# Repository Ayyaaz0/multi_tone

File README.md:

A three-band music visualiser. It takes audio signals, splits them into low (bass), mid (voice), and high (treble) bands using op-amp filters, converts each band’s loudness into a smooth control signal, and drives three LEDs via 2N3904 transistors. The circuit runs from a regulated ±12 V supply.

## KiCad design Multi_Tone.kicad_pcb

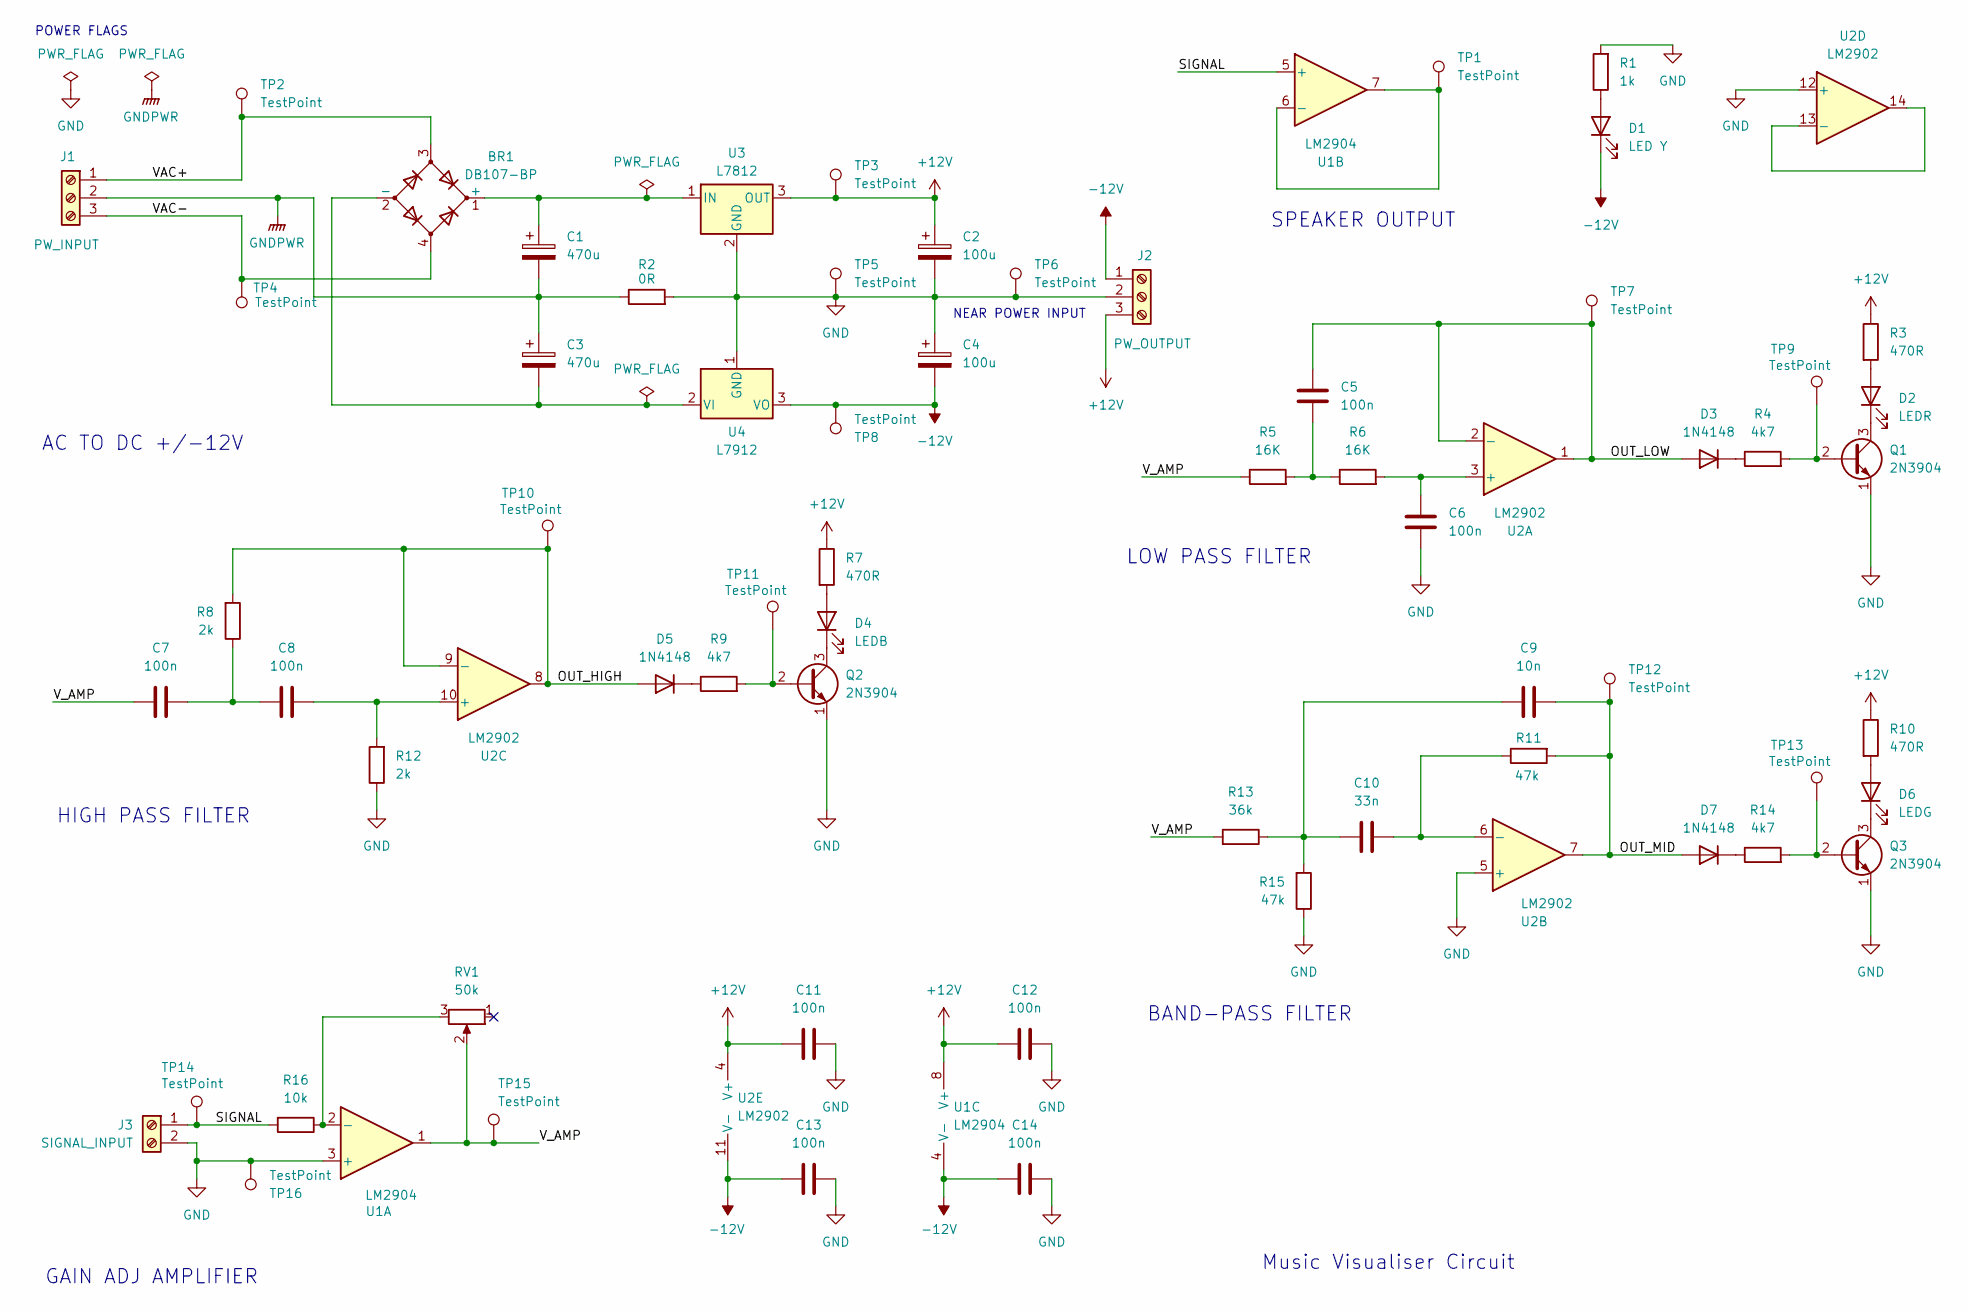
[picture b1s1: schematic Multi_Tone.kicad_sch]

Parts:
BR1: DB107-BP; Diode_Bridge_DIP-4_W7.62mm_P5.08mm
C1, C3: 470u; CP_Radial_D8.0mm_P3.50mm
C2, C4: 100u; CP_Radial_D8.0mm_P3.50mm
C5, C6, C7, C8, C11, C12, C13, C14: 100n; C_Rect_L7.0mm_W2.5mm_P5.00mm
C9: 10n; C_Rect_L7.0mm_W2.5mm_P5.00mm
C10: 33n; C_Rect_L7.0mm_W2.5mm_P5.00mm
D1: LED Y; LED_D3.0mm
D2: LEDR; LED_D3.0mm
D3, D5, D7: 1N4148; D_DO-35_SOD27_P7.62mm_Horizontal
D4: LEDB; LED_D3.0mm
D6: LEDG; LED_D3.0mm
J1: PW_INPUT; TerminalBlock_Phoenix_MKDS-1,5-3-5.08_1x03_P5.08mm_Horizont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
J2: PW_OUTPUT; TerminalBlock_Phoenix_MKDS-1,5-3-5.08_1x03_P5.08mm_Horizont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
J3: SIGNAL_INPUT; TerminalBlock_Phoenix_MKDS-1,5-2-5.08_1x02_P5.08mm_Horizont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
Q1, Q2, Q3: 2N3904; TO-92_Inline
R1: 1k; R_Axial_DIN0207_L6.3mm_D2.5mm_P10.16mm_Horizontal
R2: 0R; R_2512_6332Metric
R3, R7, R10: 470R; R_2512_6332Metric
R4, R9, R14: 4k7; R_2512_6332Metric
R5, R6: 16K; R_Axial_DIN0207_L6.3mm_D2.5mm_P10.16mm_Horizontal
R8, R12: 2k; R_Axial_DIN0207_L6.3mm_D2.5mm_P10.16mm_Horizontal
R11, R15: 47k; R_Axial_DIN0207_L6.3mm_D2.5mm_P10.16mm_Horizontal
R13: 36k; R_Axial_DIN0207_L6.3mm_D2.5mm_P10.16mm_Horizontal
R16: 10k; R_Axial_DIN0207_L6.3mm_D2.5mm_P10.16mm_Horizontal
RV1: 50k; Potentiometer_Bourns_3299W_Vertical
TP1, TP2, TP3, TP4, TP5, TP6, TP7, TP8, TP9, TP10, TP11, TP12, TP13, TP14, TP15, TP16: TestPoint; PinHeader_1x01_P2.54mm_Vertical
U1: LM2904; DIP-8_W7.62mm
U2: LM2902; DIP-14_W7.62mm
U3: L7812; TO-220-3_Vertical
U4: L7912; TO-220-3_Vertical

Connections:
+12V: C2.1, C11.1, C12.1, J2.3, R3.1, R7.1, R10.1, TP3.1, U1.8 (V+), U2.4 (V+), U3.3 (OUT)
-12V: C4.2, C13.2, C14.2, D1.1 (K), J2.1, TP8.1, U1.4 (V-), U2.11 (V-), U4.3 (VO)
/OUT_HIGH: D5.2 (A), R8.2, TP10.1, U2.8, U2.9 (-)
/OUT_LOW: C5.1, D3.2 (A), TP7.1, U2.1, U2.2 (-)
/OUT_MID: C9.2, D7.2 (A), R11.2, TP12.1, U2.7
/SIGNAL: J3.1, R16.2, TP14.1, U1.5 (+)
/V_AMP: C7.1, R5.1, R13.2, RV1.2, TP15.1, U1.1
GND: C2.2, C4.1, C6.2, C11.2, C12.2, C13.1, C14.1, J2.2, J3.2, Q1.1 (E), Q2.1 (E), Q3.1 (E), R1.2, R2.2, R12.1, R15.1, TP5.1, TP6.1, TP16.1, U1.3 (+), U2.5 (+), U2.12 (+), U3.2 (GND), U4.1 (GND)
GNDPWR: C1.2, C3.1, J1.2, R2.1
unnamed: BR1.1 (+), C1.1, U3.1 (IN)
unnamed: BR1.2 (-), C3.2, U4.2 (VI)
unnamed: C5.2, R5.2, R6.1
unnamed: C7.2, C8.1, R8.1
unnamed: C9.1, C10.1, R13.1, R15.2
unnamed: D1.2 (A), R1.1
unnamed: D2.2 (A), R3.2
unnamed: D2.1 (K), Q1.3 (C)
unnamed: D3.1 (K), R4.1
unnamed: D4.2 (A), R7.2
unnamed: D4.1 (K), Q2.3 (C)
unnamed: D5.1 (K), R9.1
unnamed: D6.2 (A), R10.2
unnamed: D6.1 (K), Q3.3 (C)
unnamed: D7.1 (K), R14.1
unnamed: BR1.3, J1.1, TP2.1
unnamed: BR1.4, J1.3, TP4.1
unnamed: Q1.2 (B), R4.2, TP9.1
unnamed: Q2.2 (B), R9.2, TP11.1
unnamed: Q3.2 (B), R14.2, TP13.1
unnamed: R16.1, RV1.3, U1.2 (-)
unnamed: TP1.1, U1.6 (-), U1.7
unnamed: C6.1, R6.2, U2.3 (+)
unnamed: C10.2, R11.1, U2.6 (-)
unnamed: C8.2, R12.2, U2.10 (+)
unnamed: U2.13 (-), U2.14

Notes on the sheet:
NEAR POWER INPUT
BAND-PASS FILTER
Music Visualiser Circuit
GAIN ADJ AMPLIFIER
AC TO DC +/-12V
HIGH PASS FILTER
POWER FLAGS
SPEAKER OUTPUT
LOW PASS FILTER

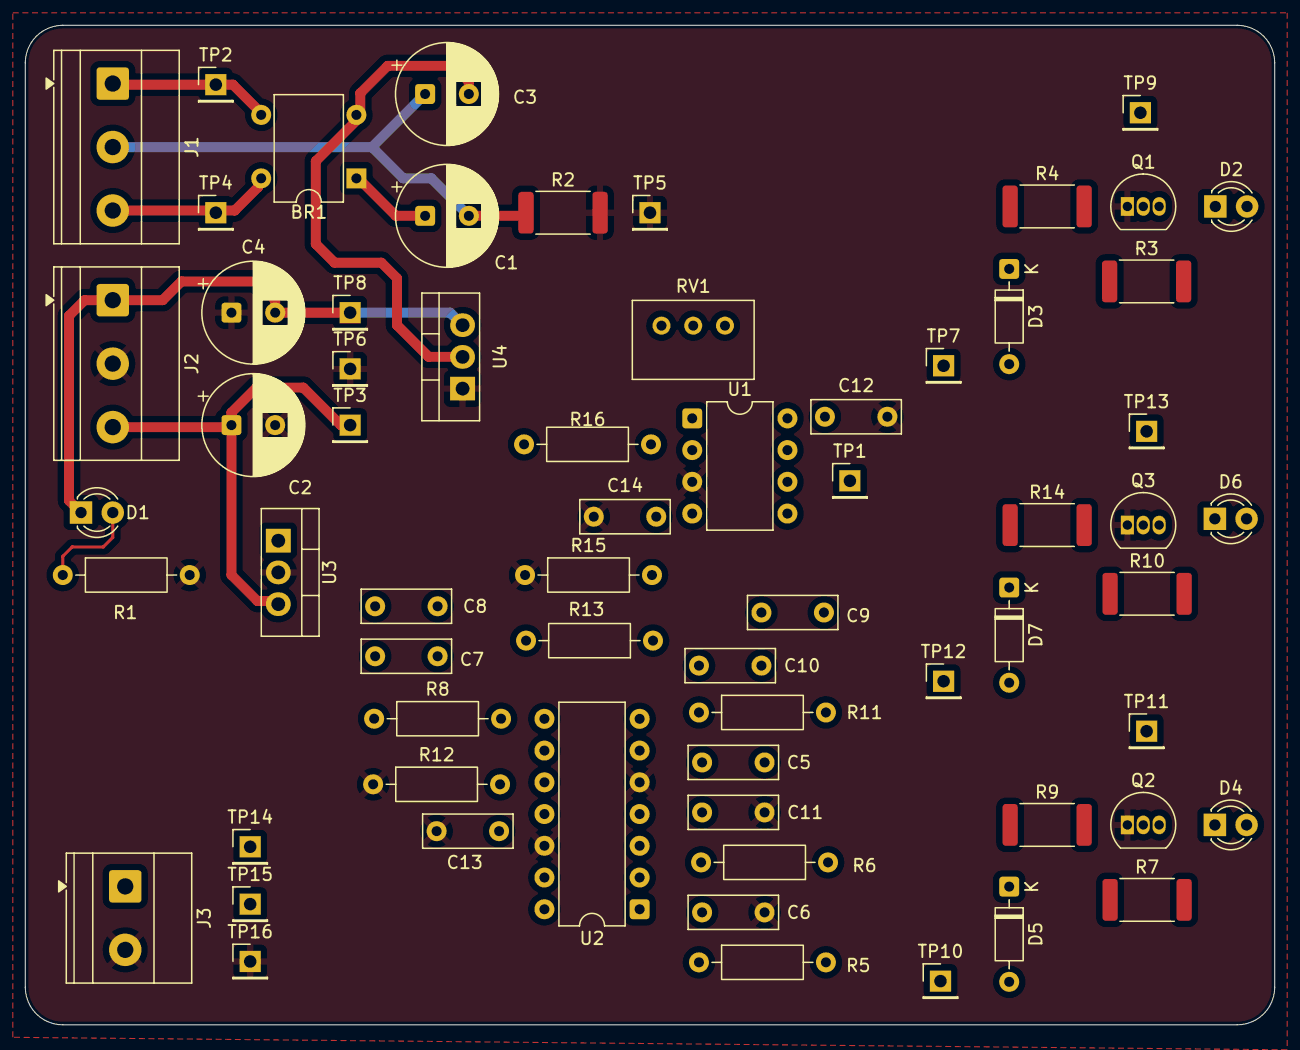
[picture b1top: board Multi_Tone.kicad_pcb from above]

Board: 2 copper layers, 100.0 x 80.0 mm, 65 parts (0 on the bottom side), 35 nets.

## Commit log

2026-02-06 Initial KiCad project
2026-02-08 Added band-pass filter, ac-dc power, low-pass filter
2026-02-13 Completed schematic layout of music visualiser circuit.
2026-02-13 Added footprints to schematic and changed band-pass filter resistor to 47k (R11)
2026-02-18 Updated PCB layout and added power tracks.
2026-02-20 Finishd PCB design
2026-02-20 Add project description to README.md
